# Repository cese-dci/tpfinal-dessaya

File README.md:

# Teensy 3.2

TP final de la materia Diseño de Circuitos Impresos - CESE - 2020A

Objetivo: Réplica del módulo [Teensy 3.2](https://www.pjrc.com/store/teensy32.html)

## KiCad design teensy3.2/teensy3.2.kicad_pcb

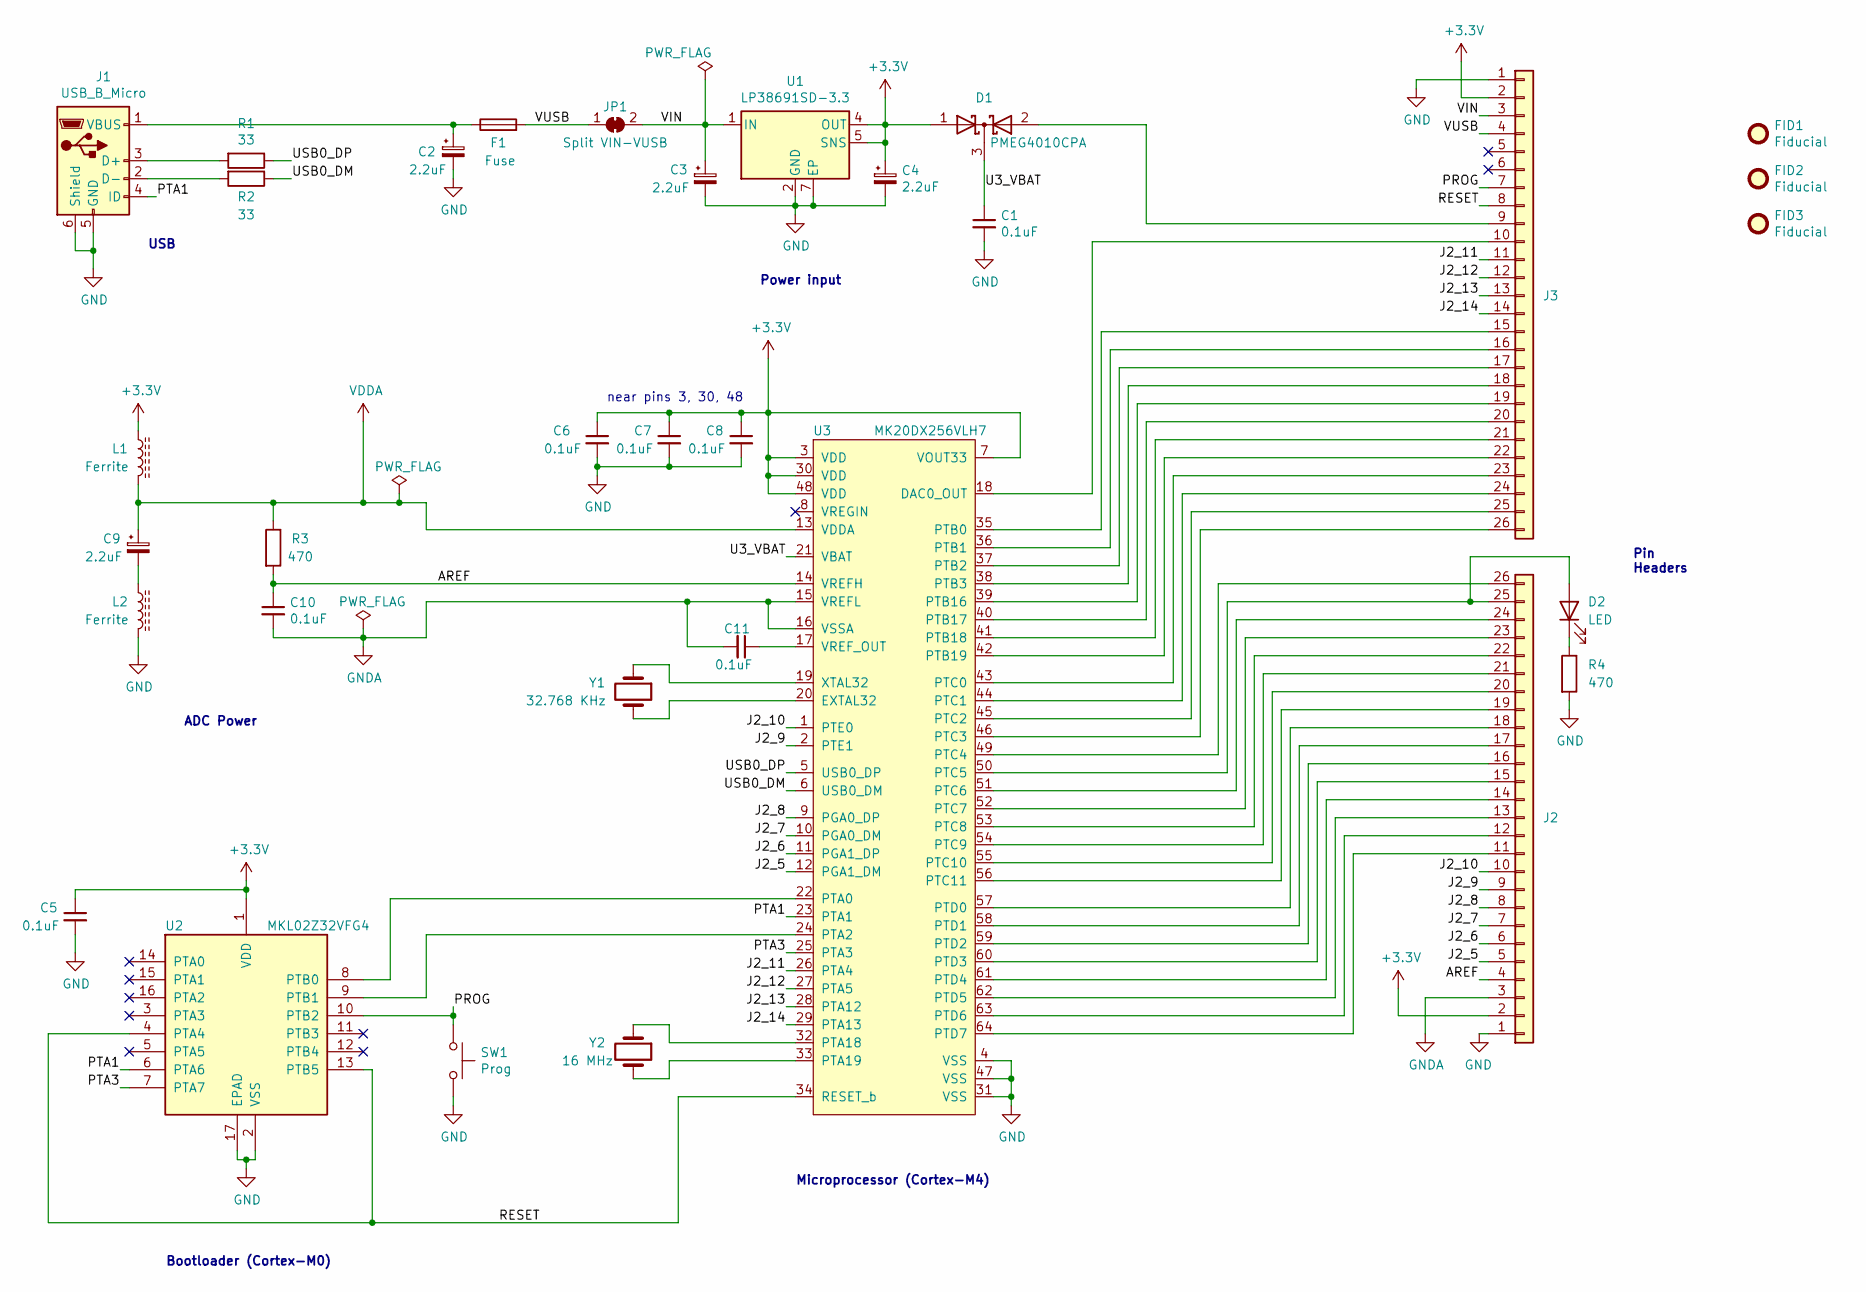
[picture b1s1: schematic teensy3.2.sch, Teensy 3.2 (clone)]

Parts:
C1, C5, C6, C7, C8, C10, C11: 0.1uF; C_0805_2012Metric
C2, C3, C4, C9: 2.2uF; C_0805_2012Metric
D1: PMEG4010CPA; HUSON-3-1EP_2x2mm_P1.3mm_EP1.1x1.6mm; Digikey# 1727-5212-2-ND
D2: LED; LED_0805_2012Metric
F1: Fuse; Fuse_0805_2012Metric
FID1, FID2, FID3: Fiducial; Fiducial_0.5mm_Mask1.5mm
J1: USB_B_Micro; USB_Micro-B_Molex_47346-0001; Digikey# 2134441-2
J2, J3: Conn_01x26; PinSocket_1x26_P2.54mm_Vertical
JP1: Split VIN-VUSB; SolderJumper-2_P1.3mm_Bridged2Bar_Pad1.0x1.5mm
L1, L2: Ferrite; L_0805_2012Metric; Digikey# 2035-0805CS-331EKFSTR-ND
R1, R2: 33; R_0805_2012Metric
R3, R4: 470; R_0805_2012Metric
SW1: Prog; SW_SPST_PTS810
U1: LP38691SD-3.3; WSON-6-1EP_3x3mm_P0.95mm; Digikey# LP38691SD-3.3/NOPBTR-ND
U2: MKL02Z32VFG4; QFN-16-1EP_3x3mm_P0.5mm_EP1.9x1.9mm; Digikey# MKL02Z32VFG4-ND
U3: MK20DX256VLH7; LQFP-64_10x10mm_P0.5mm; Digikey# MK20DX256VLH7-ND
Y1: 32.768 KHz; Crystal_SMD_2012-2Pin_2.0x1.2mm; Digikey# XC2743CT-ND
Y2: 16 MHz; Crystal_SMD_2016-4Pin_2.0x1.6mm; Digikey# XC2630TR-ND

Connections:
+3V3: C4.1, C5.1, C6.1, C7.1, C8.1, D1.1 (A), J2.2, J3.2, L1.1, U1.4 (OUT), U1.5 (SNS), U2.1 (VDD), U3.3 (VDD), U3.7 (VOUT33), U3.30 (VDD), U3.48 (VDD)
/AREF: C10.1, J2.4, R3.2, U3.14 (VREFH)
/J2_5: J2.5, U3.12 (PGA1_DM)
/J2_6: J2.6, U3.11 (PGA1_DP)
/J2_7: J2.7, U3.10 (PGA0_DM)
/J2_8: J2.8, U3.9 (PGA0_DP)
/J2_9: J2.9, U3.2 (PTE1)
/J2_10: J2.10, U3.1 (PTE0)
/J2_11: J3.11, U3.26 (PTA4)
/J2_12: J3.12, U3.27 (PTA5)
/J2_13: J3.13, U3.28 (PTA12)
/J2_14: J3.14, U3.29 (PTA13)
/PROG: J3.7, SW1.1, U2.10 (PTB2)
/PTA1: J1.4 (ID), U2.6 (PTA6), U3.23 (PTA1)
/PTA3: U2.7 (PTA7), U3.25 (PTA3)
/RESET: J3.8, U2.4 (PTA4), U2.13 (PTB5), U3.34 (RESET_b)
/U3_VBAT: C1.1, D1.3 (K), U3.21 (VBAT)
/USB0_DM: R2.1, U3.6 (USB0_DM)
/USB0_DP: R1.1, U3.5 (USB0_DP)
/VIN: C3.1, J3.3, JP1.2 (B), U1.1 (IN), U1.6 (IN)
/VUSB: F1.2, J3.4, JP1.1 (A)
GND: C1.2, C2.2, C3.2, C4.2, C5.2, C6.2, C7.2, C8.2, J1.5 (GND), J1.6 (Shield), J2.1, J3.1, L2.2, R4.2, SW1.2, U1.2 (GND), U1.7 (EP), U2.2 (VSS), U2.17 (EPAD), U3.4 (VSS), U3.31 (VSS), U3.47 (VSS)
GNDA: C10.2, C11.2, J2.3, U3.15 (VREFL), U3.16 (VSSA)
unnamed: C2.1, F1.1, J1.1 (VBUS)
unnamed: C9.2, L2.1
unnamed: C11.1, U3.17 (VREF_OUT)
unnamed: D1.2 (A), J3.9
unnamed: D2.1 (K), R4.1
unnamed: D2.2 (A), J2.25, U3.50 (PTC5)
unnamed: J1.2 (D-), R2.2
unnamed: J1.3 (D+), R1.2
unnamed: J2.11, U3.64 (PTD7)
unnamed: J2.12, U3.63 (PTD6)
unnamed: J2.13, U3.62 (PTD5)
unnamed: J2.14, U3.61 (PTD4)
unnamed: J2.15, U3.60 (PTD3)
unnamed: J2.16, U3.59 (PTD2)
unnamed: J2.17, U3.58 (PTD1)
unnamed: J2.18, U3.57 (PTD0)
unnamed: J2.19, U3.56 (PTC11)
unnamed: J2.20, U3.55 (PTC10)
unnamed: J2.21, U3.54 (PTC9)
unnamed: J2.22, U3.53 (PTC8)
unnamed: J2.23, U3.52 (PTC7)
unnamed: J2.24, U3.51 (PTC6)
unnamed: J2.26, U3.49 (PTC4)
unnamed: J3.10, U3.18 (DAC0_OUT)
unnamed: J3.15, U3.35 (PTB0)
unnamed: J3.16, U3.36 (PTB1)
unnamed: J3.17, U3.37 (PTB2)
unnamed: J3.18, U3.38 (PTB3)
unnamed: J3.19, U3.39 (PTB16)
unnamed: J3.20, U3.40 (PTB17)
unnamed: J3.21, U3.41 (PTB18)
unnamed: J3.22, U3.42 (PTB19)
unnamed: J3.23, U3.43 (PTC0)
unnamed: J3.24, U3.44 (PTC1)
unnamed: J3.25, U3.45 (PTC2)
unnamed: J3.26, U3.46 (PTC3)
unnamed: U2.8 (PTB0), U3.22 (PTA0)
unnamed: U2.9 (PTB1), U3.24 (PTA2)
unnamed: U3.19 (XTAL32), Y1.1
unnamed: U3.20 (EXTAL32), Y1.2
unnamed: U3.32 (PTA18), Y2.1
unnamed: U3.33 (PTA19), Y2.2
VDDA: C9.1, L1.2, R3.1, U3.13 (VDDA)

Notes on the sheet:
Microprocessor (Cortex-M4)
USB
Bootloader (Cortex-M0)
Power input
ADC Power
near pins 3, 30, 48
Pin Headers

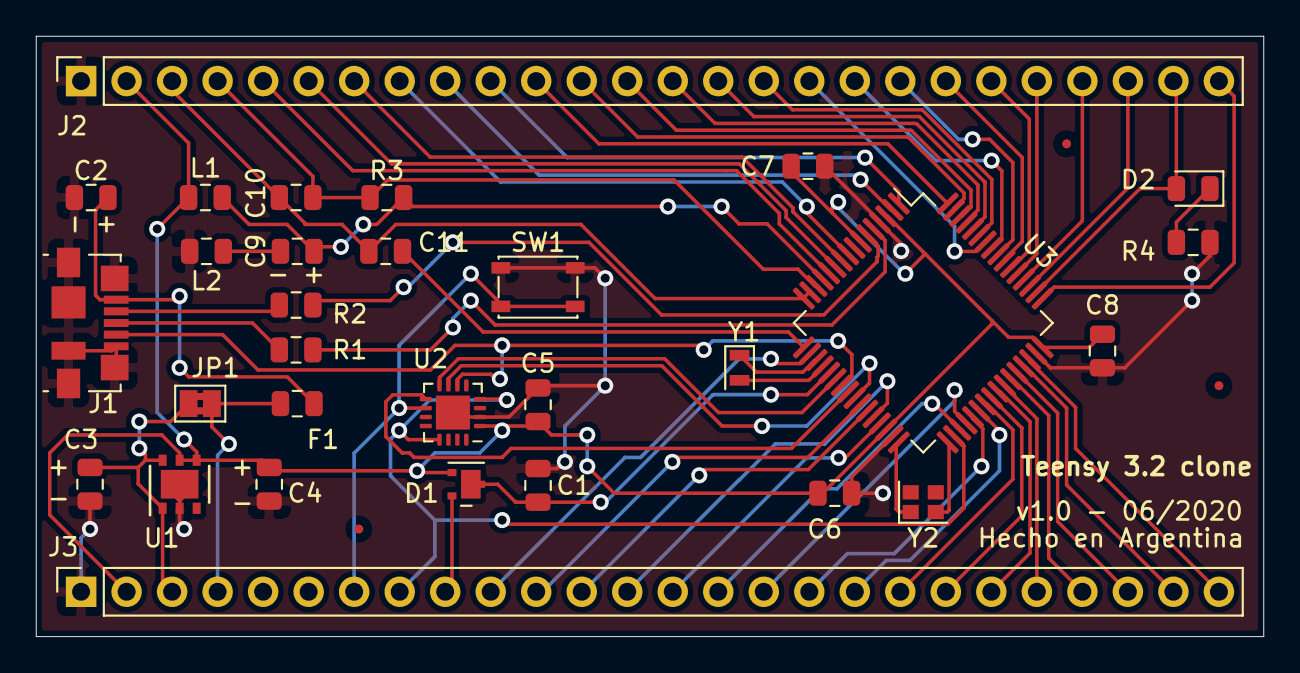
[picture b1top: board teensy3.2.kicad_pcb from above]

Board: 2 copper layers, 68.5 x 33.5 mm, 33 parts (0 on the bottom side), 66 nets.

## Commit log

2020-05-26 work in progress
2020-05-29 ERC ok
2020-06-05 asignacion de footprints lista
2020-06-06 PCB wip
2020-06-08 ajustes al esquematico
2020-06-11 avances pcb
2020-06-13 avances sch + pcb
2020-06-13 avances sch
2020-06-13 avances ruteo pcb
2020-06-14 fin ruteo pcb
2020-06-14 fin pcb
2020-06-14 ajustes
2020-06-14 ajustes revision pcb
2020-06-18 ajustes para revision final

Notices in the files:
teensy3.2/teensy3.2.kicad_pcb:
License: CC BY 4.0
